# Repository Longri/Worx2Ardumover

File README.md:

# Worx2Ardumover
Ardumover on base of Worx Landroid

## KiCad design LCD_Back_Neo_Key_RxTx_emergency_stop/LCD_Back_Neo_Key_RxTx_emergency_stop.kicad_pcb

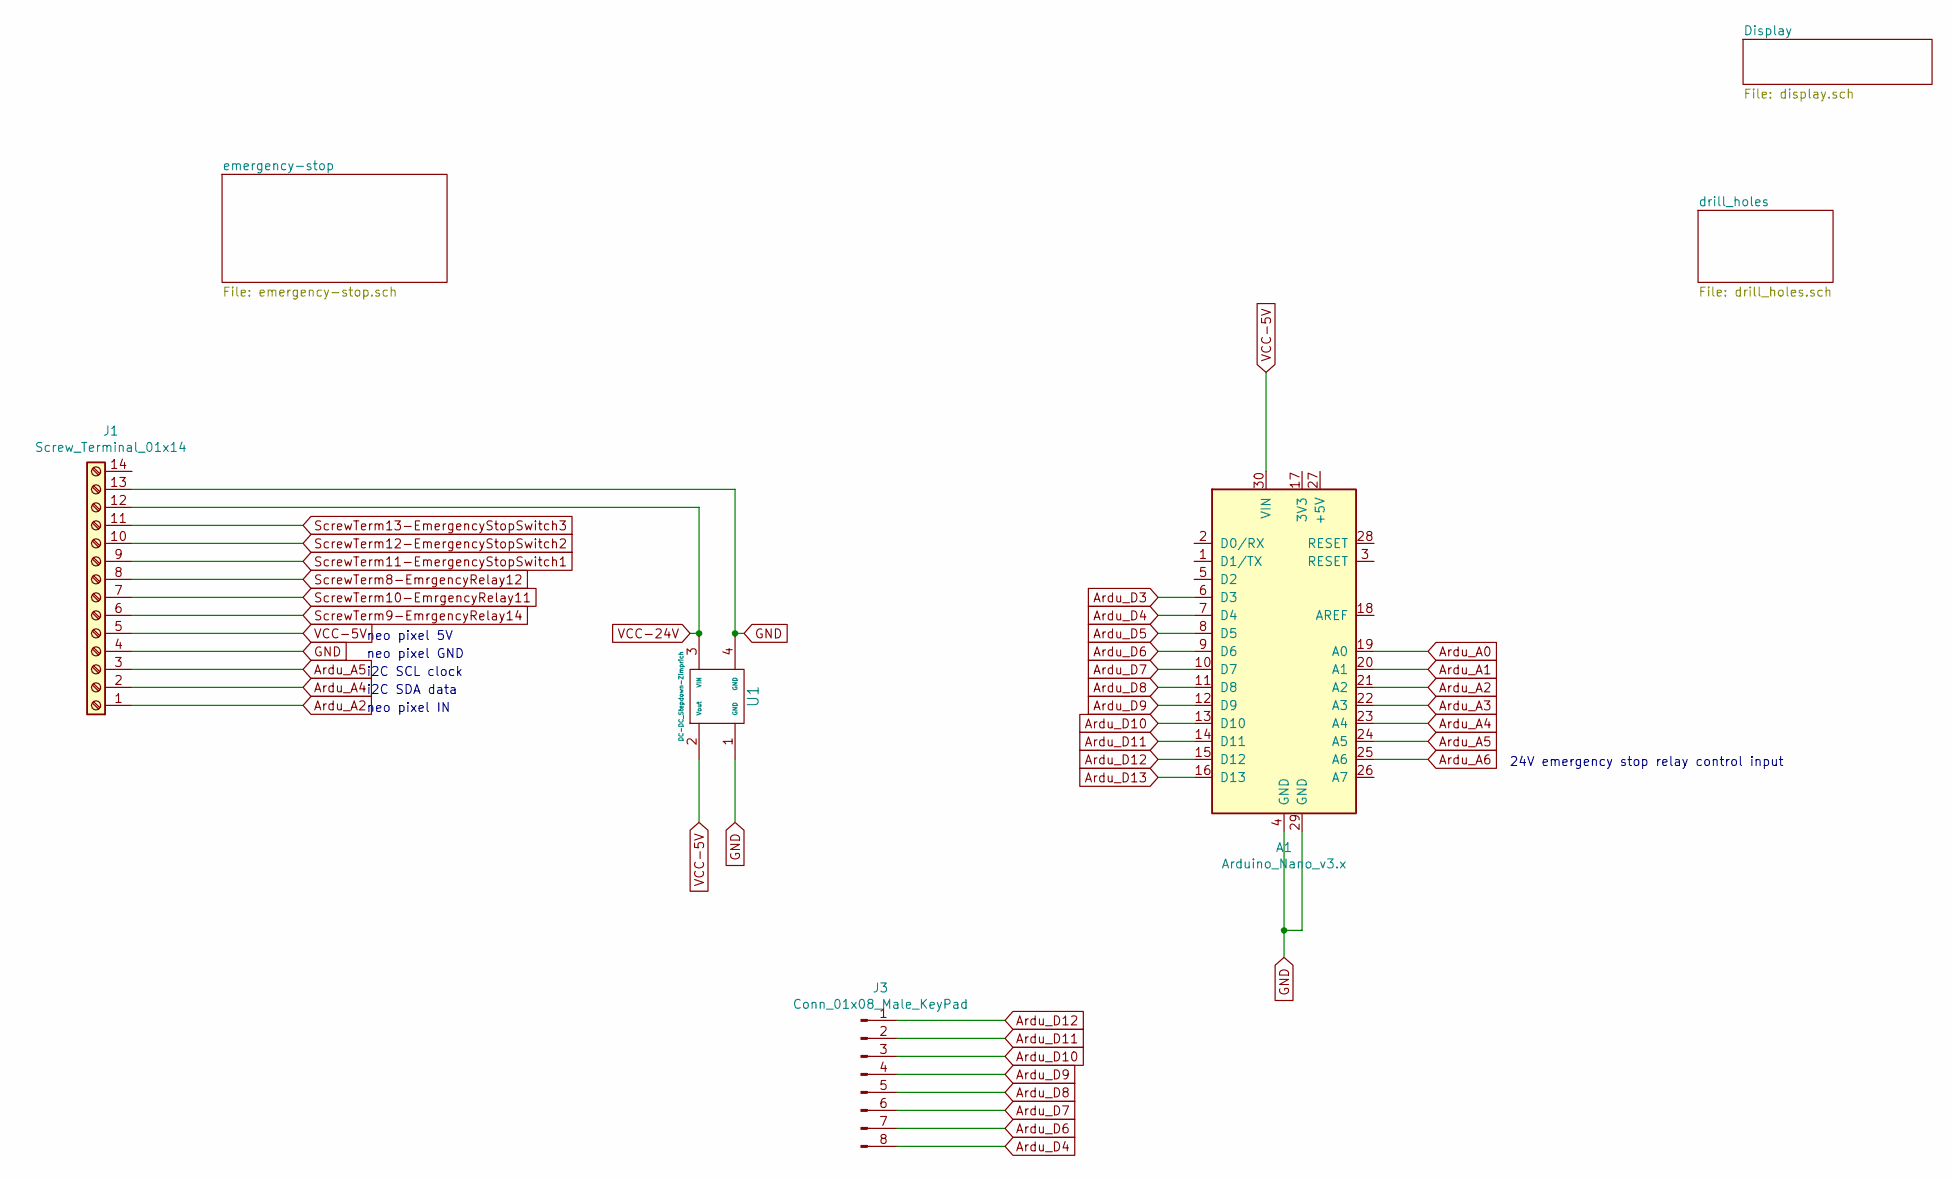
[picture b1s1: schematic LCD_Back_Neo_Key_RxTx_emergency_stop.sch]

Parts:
A1: Arduino_Nano_v3.x; Arduino_Nano_Miror
J1: Screw_Terminal_01x14; PhoenixContact_MSTBVA_2,5_14-G_1x14_P5.00mm_Vertical
J3: Conn_01x08_Male_KeyPad; PinHeader_1x08_P2.54mm_Horizontal_invert
U1: DC-DC_Stepdown-Zimprich; Converter_DCDC

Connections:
Ardu_A0: A1.19 (A0); also elsewhere on the board
Ardu_A1: A1.20 (A1); also elsewhere on the board
Ardu_A2: A1.21 (A2), J1.1
Ardu_A3: A1.22 (A3); also elsewhere on the board
Ardu_A4: A1.23 (A4), J1.2
Ardu_A5: A1.24 (A5), J1.3
Ardu_A6: A1.25 (A6); also elsewhere on the board
Ardu_D3: A1.6 (D3); also elsewhere on the board
Ardu_D4: A1.7 (D4), J3.8
Ardu_D5: A1.8 (D5); also elsewhere on the board
Ardu_D6: A1.9 (D6), J3.7
Ardu_D7: A1.10 (D7), J3.6
Ardu_D8: A1.11 (D8), J3.5
Ardu_D9: A1.12 (D9), J3.4
Ardu_D10: A1.13 (D10), J3.3
Ardu_D11: A1.14 (D11), J3.2
Ardu_D12: A1.15 (D12), J3.1
Ardu_D13: A1.16 (D13); also elsewhere on the board
GND: A1.4 (GND), A1.29 (GND), J1.4, J1.10, J1.13, U1.1 (GND), U1.4 (GND); also elsewhere on the board
ScrewTerm8-EmrgencyRelay12: J1.8; also elsewhere on the board
ScrewTerm9-EmrgencyRelay14: J1.6; also elsewhere on the board
ScrewTerm10-EmrgencyRelay11: J1.7; also elsewhere on the board
ScrewTerm11-EmergencyStopSwitch1: J1.9; also elsewhere on the board
ScrewTerm13-EmergencyStopSwitch3: J1.11; also elsewhere on the board
VCC-5V: A1.30 (VIN), J1.5, U1.2 (Vout); also elsewhere on the board
VCC-24V: J1.12, U1.3 (VIN); also elsewhere on the board

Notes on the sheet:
24V emergency stop relay control input
neo pixel IN
neo pixel GND
neo pixel 5V
i2C SCL clock
i2C SDA data

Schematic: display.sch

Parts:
C1: CP; CP_Radial_D8.0mm_P2.50mm
J2: Conn_01x20_Female; Display
Q1: BC337; TO-92_Inline
R1: R; R_Axial_DIN0207_L6.3mm_D2.5mm_P10.16mm_Horizontal
R2: R; R_Axial_DIN0207_L6.3mm_D2.5mm_P15.24mm_Horizontal

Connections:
Ardu_A0: J2.17; also elsewhere on the board
Ardu_A1: J2.16; also elsewhere on the board
Ardu_D3: R2.2; also elsewhere on the board
Ardu_D5: R1.2; also elsewhere on the board
Ardu_D13: J2.15; also elsewhere on the board
GND: C1.2, J2.6, J2.20, Q1.3; also elsewhere on the board
unnamed: C1.1, J2.18, R2.1
unnamed: J2.1, Q1.1
unnamed: Q1.2, R1.1
VCC-5V: J2.2, J2.19; also elsewhere on the board

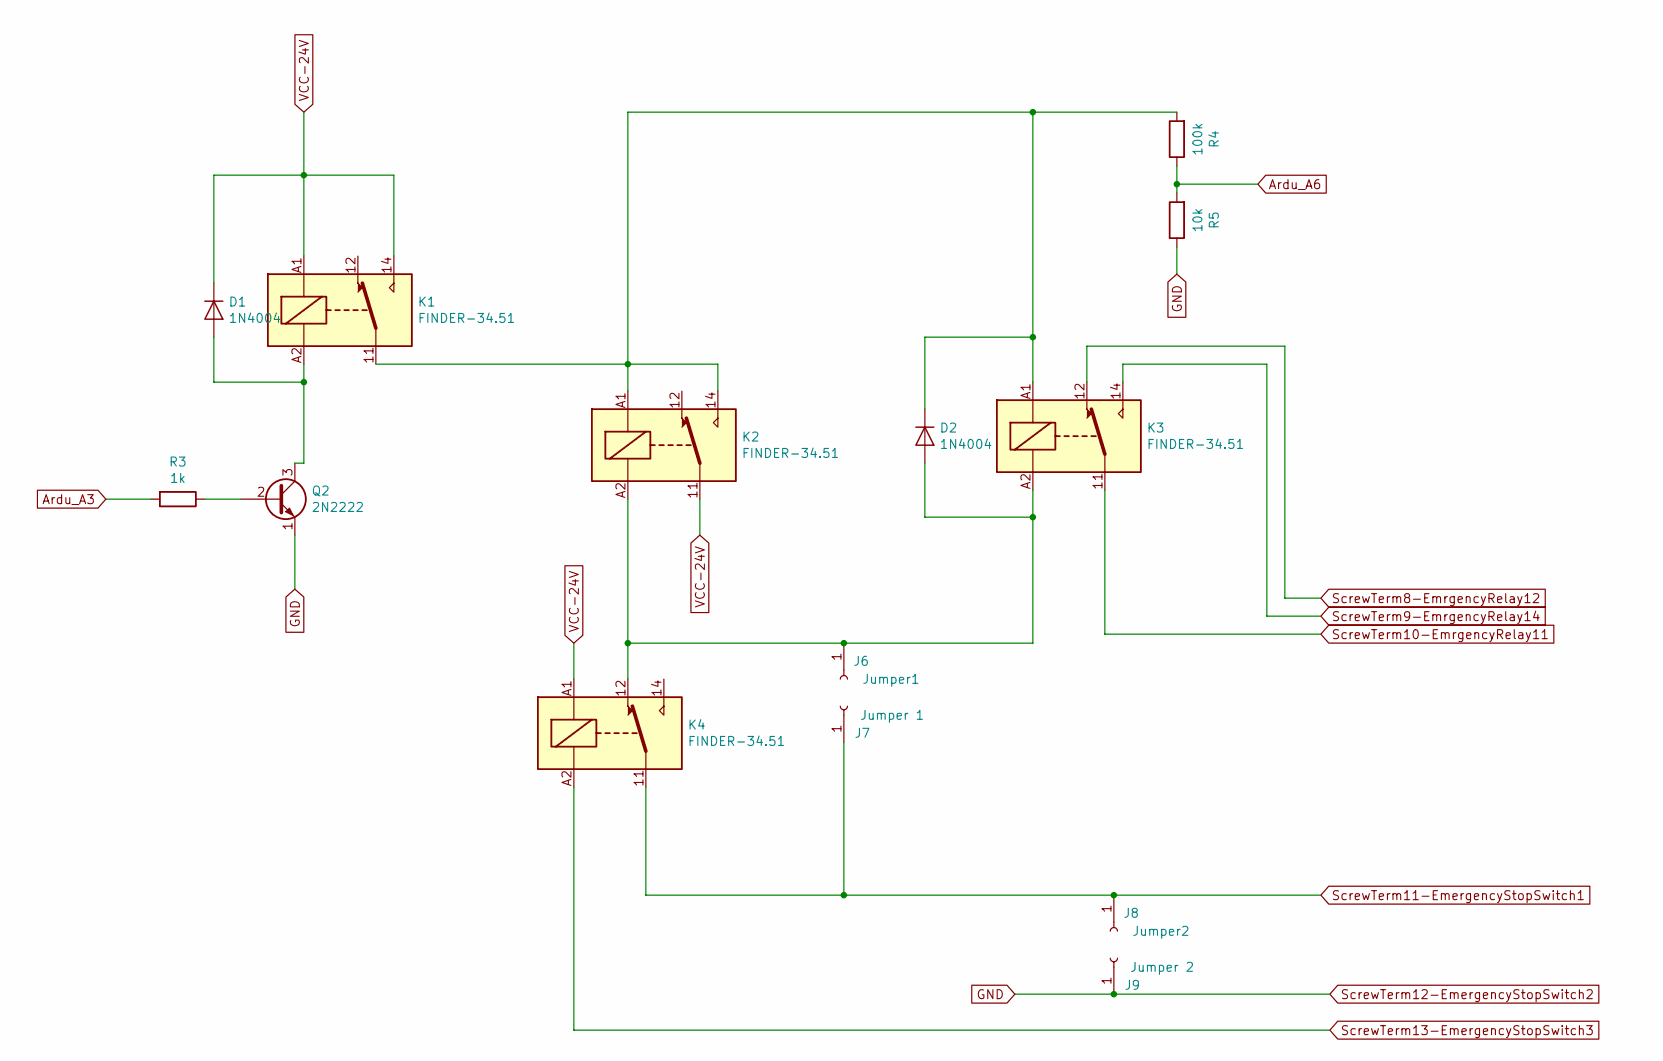
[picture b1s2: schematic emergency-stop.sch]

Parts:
D1, D2: 1N4004; D_DO-41_SOD81_P10.16mm_Horizontal
J6: Jumper1; Pin_D0.7mm_L6.5mm_W1.8mm_FlatFork
J7: Jumper 1; Pin_D0.7mm_L6.5mm_W1.8mm_FlatFork
J8: Jumper2; Pin_D0.7mm_L6.5mm_W1.8mm_FlatFork
J9: Jumper 2; Pin_D0.7mm_L6.5mm_W1.8mm_FlatFork
K1, K2, K3, K4: FINDER-34.51; Relay_SPDT_Finder_34.51_Vertical
Q2: 2N2222; TO-39-3
R3: 1k; R_Axial_DIN0207_L6.3mm_D2.5mm_P10.16mm_Horizontal
R4: 100k; R_Axial_DIN0207_L6.3mm_D2.5mm_P10.16mm_Horizontal
R5: 10k; R_Axial_DIN0207_L6.3mm_D2.5mm_P10.16mm_Horizontal

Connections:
Ardu_A3: R3.2; also elsewhere on the board
Ardu_A6: R4.1, R5.2; also elsewhere on the board
GND: J9.1, Q2.1 (E), R5.1; also elsewhere on the board
unnamed: D1.2 (A), K1.A2, Q2.3 (C)
unnamed: D2.1 (K), K1.11, K2.14, K2.A1, K3.A1, R4.2
unnamed: D2.2 (A), J6.1, K2.A2, K3.A2, K4.12
unnamed: Q2.2 (B), R3.1
ScrewTerm8-EmrgencyRelay12: K3.12; also elsewhere on the board
ScrewTerm9-EmrgencyRelay14: K3.14; also elsewhere on the board
ScrewTerm10-EmrgencyRelay11: K3.11; also elsewhere on the board
ScrewTerm11-EmergencyStopSwitch1: J7.1, J8.1, K4.11; also elsewhere on the board
ScrewTerm13-EmergencyStopSwitch3: K4.A2; also elsewhere on the board
VCC-24V: D1.1 (K), K1.14, K1.A1, K2.11, K4.A1; also elsewhere on the board

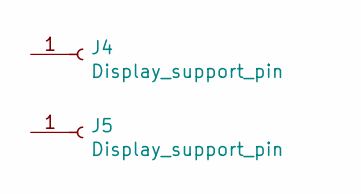
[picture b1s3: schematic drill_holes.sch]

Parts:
J4, J5: Display_support_pin; Pin_D0.7mm_L6.5mm_W1.8mm_FlatFork

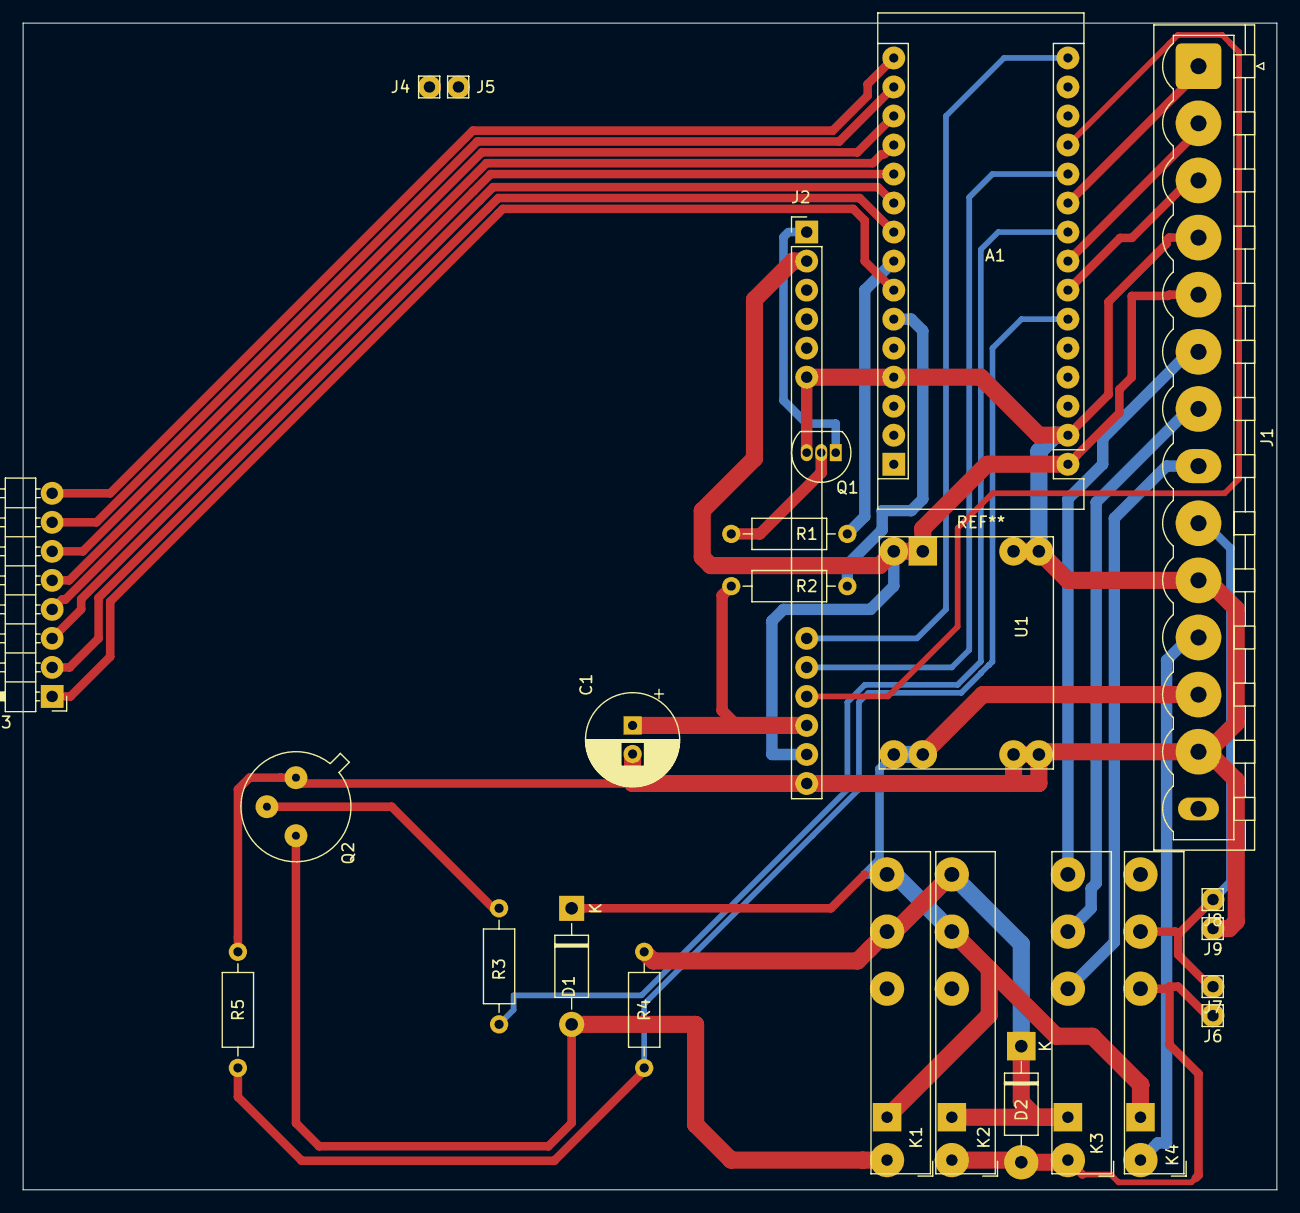
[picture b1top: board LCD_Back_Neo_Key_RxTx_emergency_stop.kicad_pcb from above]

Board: 2 copper layers, 109.7 x 102.1 mm, 25 parts (0 on the bottom side), 33 nets.

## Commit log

2019-05-21 upload project files for PCB LCD_Back_Neo_Key_RxTx_emergency_stop
2019-05-21 change Pin for PIN_NEOPIXE from 19(A6) to 16(A2)
2019-05-21 Add Powersuplay for LCD on FRitzing
2019-05-28 add new sheet 'Display'
2019-05-28 add sheet for emergency stop
2019-05-29 add freewheeling diode for relays
2019-05-29 add gitignore
2019-05-29 remove ABCCDEF....
2019-05-29 remove backup file
2019-05-30 remove and ignore *.bak files
2019-05-30 combine screw terminal
2019-06-06 add folder for used kicad libs
2019-06-06 revert *.lib from gitignore
2019-06-06 add a missing lib
2019-06-07 integreate fritzing test for emergency stop relay
2019-06-13 place screwterminal on PCB
2019-06-13 contact all on PCB
2019-06-13 move keyboard connector
2019-06-14 add mouting holes
2019-06-18 make mounting holes free from tracks
2019-06-18 remove all through-connection. Manufacturer can't handle
2019-06-28 grow up Pads
2019-06-28 remove screw holes
2019-06-28 new Gerber files
